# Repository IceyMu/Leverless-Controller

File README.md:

# Leverless-Controller
 A Leverless Controller for Fighting Games

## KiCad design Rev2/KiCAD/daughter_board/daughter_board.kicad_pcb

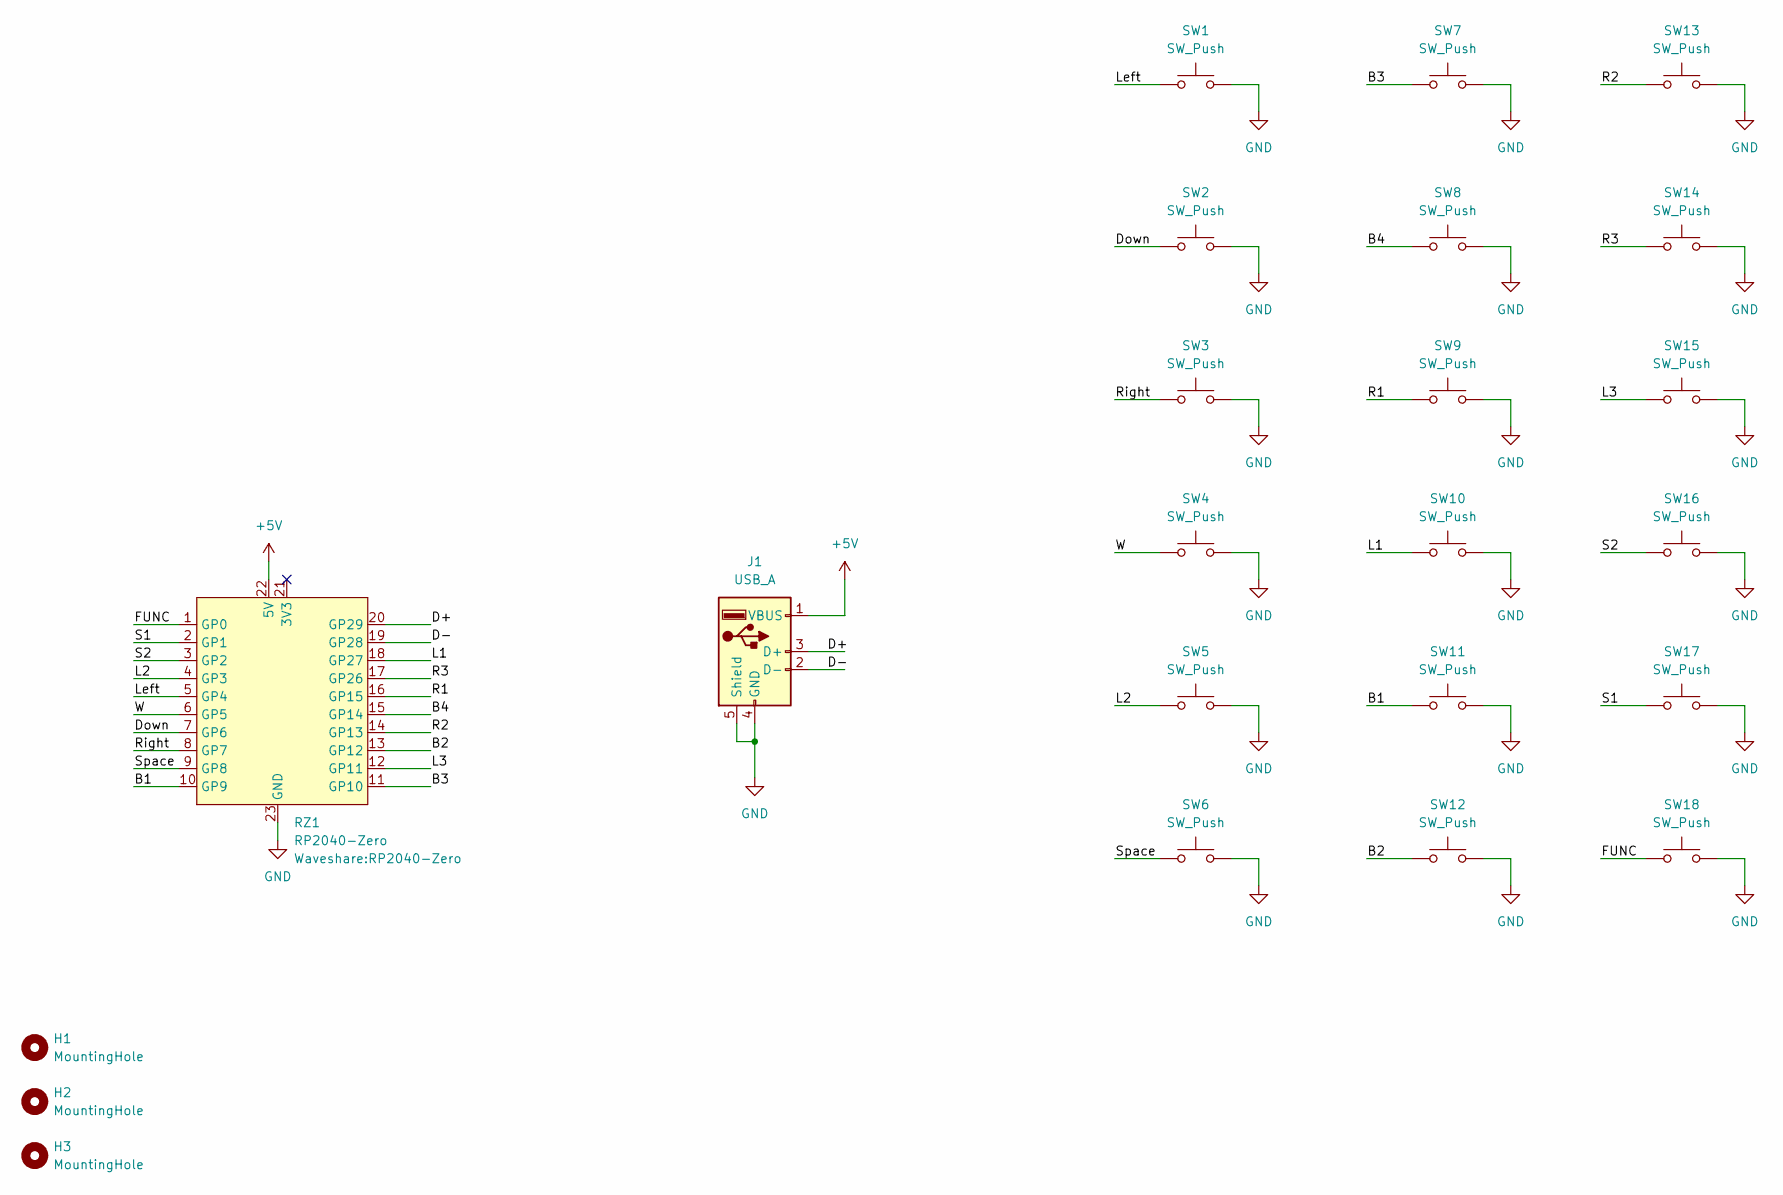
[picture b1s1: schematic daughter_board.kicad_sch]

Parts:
H1, H2, H3: MountingHole; MountingHole_3.2mm_M3
J1: USB_A; USB_A_TE_292303-7_Horizontal
RZ1: RP2040-Zero
SW1, SW2, SW3, SW4, SW5, SW6, SW7, SW8, SW9, SW10, SW11, SW12, SW13, SW14, SW15: SW_Push; SW_Gateron_LowProfile_THT
SW16, SW17, SW18: SW_Push; 6x6 vertical button

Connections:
+5V: J1.1 (VBUS), RZ1.22 (5V)
/B1: RZ1.10 (GP9), SW11.1
/B2: RZ1.13 (GP12), SW12.1
/B3: RZ1.11 (GP10), SW7.1
/B4: RZ1.15 (GP14), SW8.1
/D+: J1.3 (D+), RZ1.20 (GP29)
/D-: J1.2 (D-), RZ1.19 (GP28)
/Down: RZ1.7 (GP6), SW2.1
/FUNC: RZ1.1 (GP0), SW18.1
/L1: RZ1.18 (GP27), SW10.1
/L2: RZ1.4 (GP3), SW5.1
/L3: RZ1.12 (GP11), SW15.1
/Left: RZ1.5 (GP4), SW1.1
/R1: RZ1.16 (GP15), SW9.1
/R2: RZ1.14 (GP13), SW13.1
/R3: RZ1.17 (GP26), SW14.1
/Right: RZ1.8 (GP7), SW3.1
/S1: RZ1.2 (GP1), SW17.1
/S2: RZ1.3 (GP2), SW16.1
/Space: RZ1.9 (GP8), SW6.1
/W: RZ1.6 (GP5), SW4.1
GND: J1.4 (GND), J1.5 (Shield), RZ1.23 (GND), SW1.2, SW2.2, SW3.2, SW4.2, SW5.2, SW6.2, SW7.2, SW8.2, SW9.2, SW10.2, SW11.2, SW12.2, SW13.2, SW14.2, SW15.2, SW16.2, SW17.2, SW18.2

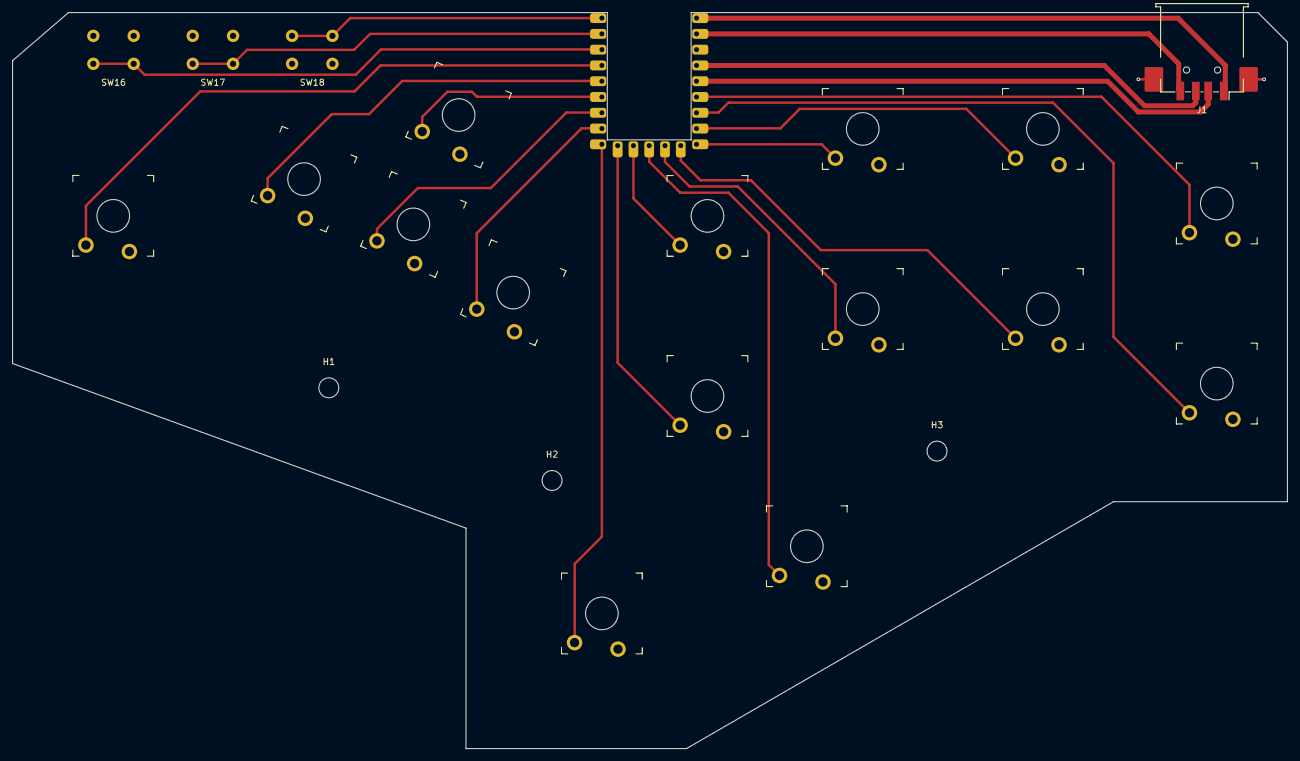
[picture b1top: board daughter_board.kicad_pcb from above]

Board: 2 copper layers, 205.2 x 118.5 mm, 23 parts (1 on the bottom side), 22 nets.

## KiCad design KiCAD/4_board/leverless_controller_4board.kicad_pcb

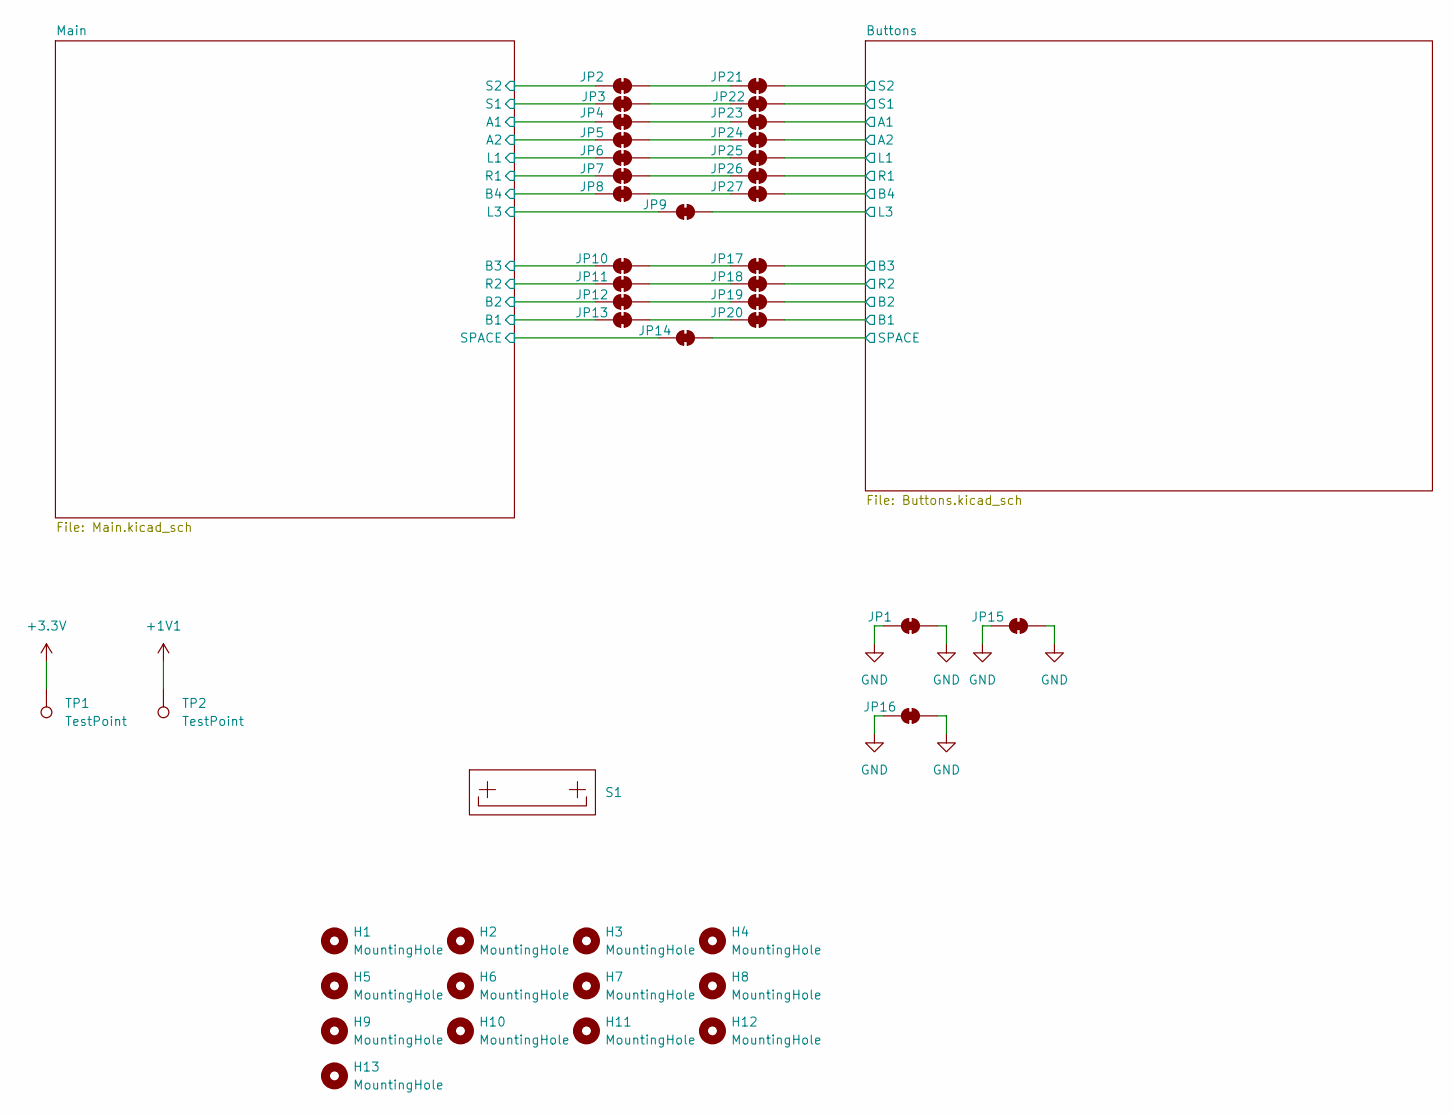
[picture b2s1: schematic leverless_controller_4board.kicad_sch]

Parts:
H1, H2, H3, H4, H5, H6, H7, H8, H9, H10, H11, H12, H13: MountingHole; MountingHole_3.2mm_M3
JP1, JP2, JP3, JP4, JP5, JP6, JP7, JP8, JP9, JP10, JP11, JP12, JP13, JP14, JP15, JP16, JP17, JP18, JP19, JP20, JP21, JP22, JP23, JP24, JP25, JP26, JP27: SolderJumper_2_Bridged; EdgeSolderJumper-2_P1.3mm_Bridged_RoundedPad1.0x1.5mm
S1: Stabilizer_Cherry_MX_2.00u
TP1, TP2: TestPoint; TestPoint_THTPad_1.0x1.0mm_Drill0.5mm

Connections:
+1V1: TP2.1; also elsewhere on the board
+3.3V: TP1.1; also elsewhere on the board
/Buttons/A1: JP23.2 (B); also elsewhere on the board
/Buttons/A2: JP24.2 (B); also elsewhere on the board
/Buttons/B1: JP20.2 (B); also elsewhere on the board
/Buttons/B2: JP19.2 (B); also elsewhere on the board
/Buttons/B3: JP17.2 (B); also elsewhere on the board
/Buttons/B4: JP27.2 (B); also elsewhere on the board
/Buttons/L1: JP25.2 (B); also elsewhere on the board
/Buttons/L3: JP9.2 (B); also elsewhere on the board
/Buttons/R1: JP26.2 (B); also elsewhere on the board
/Buttons/R2: JP18.2 (B); also elsewhere on the board
/Buttons/S1: JP22.2 (B); also elsewhere on the board
/Buttons/S2: JP21.2 (B); also elsewhere on the board
/Buttons/SPACE: JP14.2 (B); also elsewhere on the board
/Main/A1: JP4.1 (A); also elsewhere on the board
/Main/A2: JP5.1 (A); also elsewhere on the board
/Main/B1: JP13.1 (A); also elsewhere on the board
/Main/B2: JP12.1 (A); also elsewhere on the board
/Main/B3: JP10.1 (A); also elsewhere on the board
/Main/B4: JP8.1 (A); also elsewhere on the board
/Main/L1: JP6.1 (A); also elsewhere on the board
/Main/L3: JP9.1 (A); also elsewhere on the board
/Main/R1: JP7.1 (A); also elsewhere on the board
/Main/R2: JP11.1 (A); also elsewhere on the board
/Main/S1: JP3.1 (A); also elsewhere on the board
/Main/S2: JP2.1 (A); also elsewhere on the board
/Main/SPACE: JP14.1 (A); also elsewhere on the board
GND: JP1.1 (A), JP1.2 (B), JP15.1 (A), JP15.2 (B), JP16.1 (A), JP16.2 (B); also elsewhere on the board
unnamed: JP2.2 (B), JP21.1 (A)
unnamed: JP10.2 (B), JP17.1 (A)
unnamed: JP11.2 (B), JP18.1 (A)
unnamed: JP12.2 (B), JP19.1 (A)
unnamed: JP13.2 (B), JP20.1 (A)
unnamed: JP3.2 (B), JP22.1 (A)
unnamed: JP4.2 (B), JP23.1 (A)
unnamed: JP5.2 (B), JP24.1 (A)
unnamed: JP6.2 (B), JP25.1 (A)
unnamed: JP7.2 (B), JP26.1 (A)
unnamed: JP8.2 (B), JP27.1 (A)

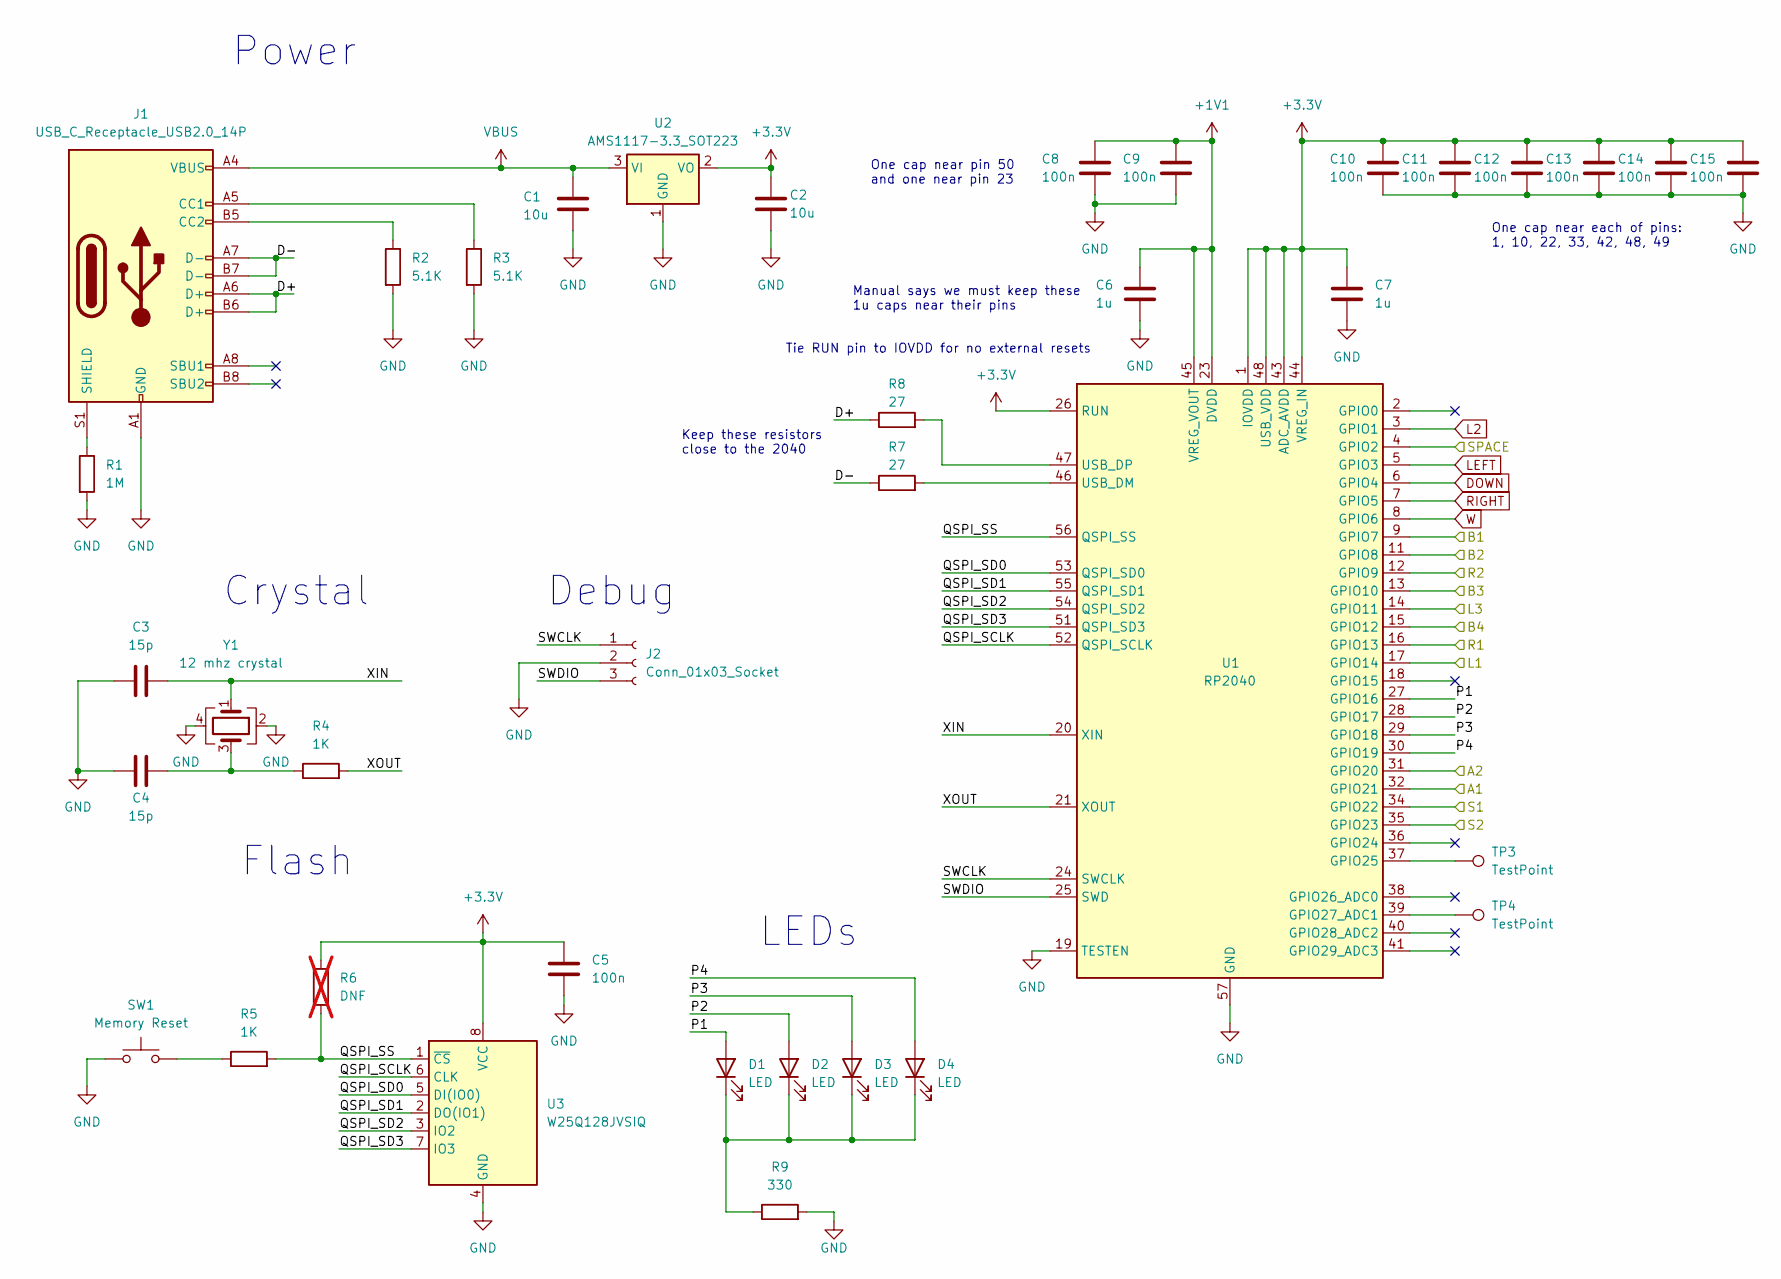
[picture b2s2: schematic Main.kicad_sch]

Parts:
C1, C2: 10u; C_0402_1005Metric; LCSC C15525
C3, C4: 15p; C_0402_1005Metric; LCSC C1548
C5, C8, C9, C10, C11, C12, C13, C14, C15: 100n; C_0402_1005Metric; LCSC C1525
C6, C7: 1u; C_0402_1005Metric; LCSC C52923
D1, D2, D3, D4: LED; LED_0805_2012Metric
J1: USB_C_Receptacle_USB2.0_14P; USB_C_Receptacle_C6332272; LCSC C6332272
J2: Conn_01x03_Socket; Debug_Points
R1: 1M; R_0402_1005Metric; LCSC C26083
R2, R3: 5.1K; R_0402_1005Metric; LCSC C25905
R4, R5: 1K; R_0402_1005Metric; LCSC C11702
R6: DNF; R_0402_1005Metric_Pad0.72x0.64mm_HandSolder; not fitted
R7, R8: 27; R_0402_1005Metric; LCSC C25190
R9: 330; R_0402_1005Metric; LCSC C25104
SW1: Memory Reset; SW_TS-1187A-C-A-B; LCSC C318884
TP3, TP4: TestPoint; TestPoint_Pad_D1.0mm
U1: RP2040; QFN-56-1EP_7x7mm_P0.4mm_EP3.2x3.2mm; LCSC C2040
U2: AMS1117-3.3_SOT223; LDO_AMS1117-3.3; LCSC C6186
U3: W25Q128JVSIQ; SOIC-8_5.23x5.23mm_P1.27mm; LCSC C97521
Y1: 12 mhz crystal; Crystal_SMD_3225-4Pin_3.2x2.5mm; LCSC C9002

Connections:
+1V1: C6.1, C8.1, C9.1, U1.23 (DVDD), U1.45 (VREG_VOUT), U1.50 (DVDD); also elsewhere on the board
+3.3V: C2.1, C5.1, C7.1, C10.1, C11.1, C12.1, C13.1, C14.1, C15.1, R6.1, U1.1 (IOVDD), U1.10 (IOVDD), U1.22 (IOVDD), U1.26 (RUN), U1.33 (IOVDD), U1.42 (IOVDD), U1.43 (ADC_AVDD), U1.44 (VREG_IN), U1.48 (USB_VDD), U1.49 (IOVDD), U2.2 (VO), U3.8 (VCC); also elsewhere on the board
/Main/A1: U1.32 (GPIO21); also elsewhere on the board
/Main/A2: U1.31 (GPIO20); also elsewhere on the board
/Main/B1: U1.9 (GPIO7); also elsewhere on the board
/Main/B2: U1.11 (GPIO8); also elsewhere on the board
/Main/B3: U1.13 (GPIO10); also elsewhere on the board
/Main/B4: U1.15 (GPIO12); also elsewhere on the board
/Main/D+: J1.A6 (D+), J1.B6 (D+), R8.1
/Main/D-: J1.A7 (D-), J1.B7 (D-), R7.1
/Main/L1: U1.17 (GPIO14); also elsewhere on the board
/Main/L3: U1.14 (GPIO11); also elsewhere on the board
/Main/P1: D1.2 (A), U1.27 (GPIO16)
/Main/P2: D2.2 (A), U1.28 (GPIO17)
/Main/P3: D3.2 (A), U1.29 (GPIO18)
/Main/P4: D4.2 (A), U1.30 (GPIO19)
/Main/QSPI_SCLK: U1.52 (QSPI_SCLK), U3.6 (CLK)
/Main/QSPI_SD0: U1.53 (QSPI_SD0), U3.5 (DI(IO0))
/Main/QSPI_SD1: U1.55 (QSPI_SD1), U3.2 (DO(IO1))
/Main/QSPI_SD2: U1.54 (QSPI_SD2), U3.3 (IO2)
/Main/QSPI_SD3: U1.51 (QSPI_SD3), U3.7 (IO3)
/Main/QSPI_SS: R5.2, R6.2, U1.56 (QSPI_SS), U3.1 (~CS)
/Main/R1: U1.16 (GPIO13); also elsewhere on the board
/Main/R2: U1.12 (GPIO9); also elsewhere on the board
/Main/S1: U1.34 (GPIO22); also elsewhere on the board
/Main/S2: U1.35 (GPIO23); also elsewhere on the board
/Main/SPACE: U1.4 (GPIO2); also elsewhere on the board
/Main/SWCLK: J2.1, U1.24 (SWCLK)
/Main/SWDIO: J2.3, U1.25 (SWD)
/Main/XIN: C3.2, U1.20 (XIN), Y1.1
/Main/XOUT: R4.2, U1.21 (XOUT)
DOWN: U1.6 (GPIO4); also elsewhere on the board
GND: C1.2, C2.2, C3.1, C4.1, C5.2, C6.2, C7.2, C8.2, C9.2, C10.2, C11.2, C12.2, C13.2, C14.2, C15.2, J1.A1 (GND), J1.A12 (GND), J1.B1 (GND), J1.B12 (GND), J2.2, R1.2, R2.2, R3.2, R9.2, SW1.1, U1.19 (TESTEN), U1.57 (GND), U2.1 (GND), U3.4 (GND), Y1.2, Y1.4; also elsewhere on the board
L2: U1.3 (GPIO1); also elsewhere on the board
LEFT: U1.5 (GPIO3); also elsewhere on the board
unnamed: C4.2, R4.1, Y1.3
unnamed: D1.1 (K), D2.1 (K), D3.1 (K), D4.1 (K), R9.1
unnamed: J1.A5 (CC1), R3.1
unnamed: J1.B5 (CC2), R2.1
unnamed: J1.S1 (SHIELD), R1.1
unnamed: R5.1, SW1.2
unnamed: TP3.1, U1.37 (GPIO25)
unnamed: TP4.1, U1.39 (GPIO27_ADC1)
unnamed: R7.2, U1.46 (USB_DM)
unnamed: R8.2, U1.47 (USB_DP)
RIGHT: U1.7 (GPIO5); also elsewhere on the board
VBUS: C1.1, J1.A4 (VBUS), J1.A9 (VBUS), J1.B4 (VBUS), J1.B9 (VBUS), U2.3 (VI)
W: U1.8 (GPIO6); also elsewhere on the board

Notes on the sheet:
Crystal
Keep these resistors close to the 2040
Flash
Tie RUN pin to IOVDD for no external resets
Debug
One cap near each of pins: 1, 10, 22, 33, 42, 48, 49
Manual says we must keep these 1u caps near their pins
One cap near pin 50 and one near pin 23
LEDs
Power

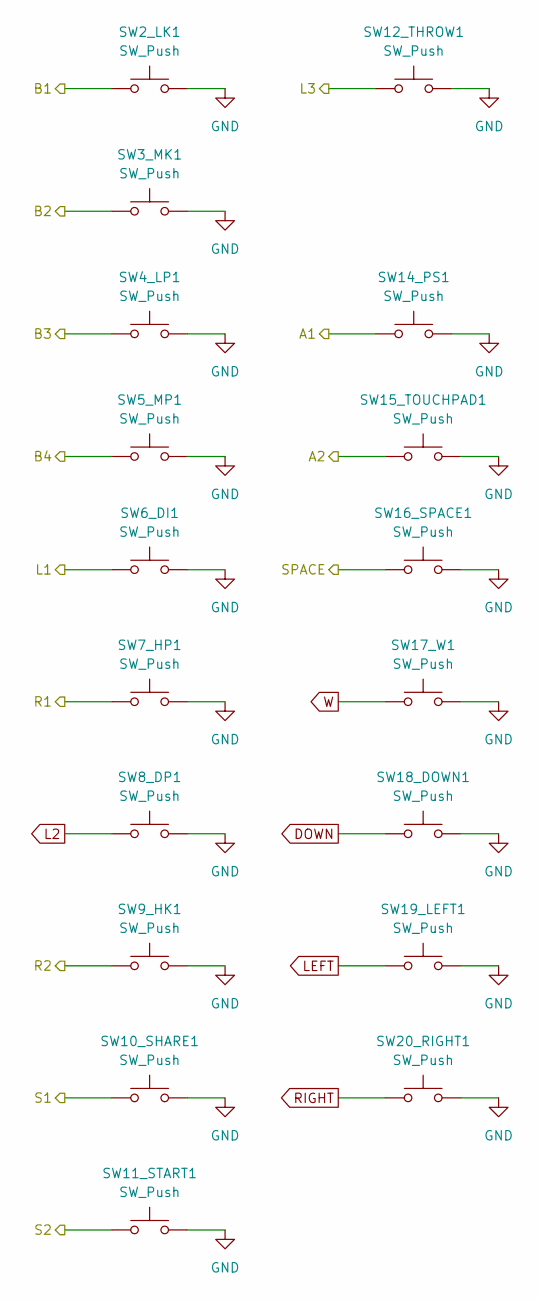
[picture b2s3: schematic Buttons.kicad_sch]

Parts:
SW2_LK1, SW3_MK1, SW4_LP1, SW5_MP1, SW6_DI1, SW7_HP1, SW8_DP1, SW9_HK1, SW12_THROW1, SW16_SPACE1: SW_Push; SW_Cherry_MX_PCB
SW10_SHARE1, SW11_START1, SW14_PS1, SW15_TOUCHPAD1: SW_Push; SW_SPST_6x12
SW17_W1, SW18_DOWN1, SW19_LEFT1, SW20_RIGHT1: SW_Push; SW_Cherry_MX_PCB_1.00u

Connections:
/Buttons/A1: SW14_PS1.1; also elsewhere on the board
/Buttons/A2: SW15_TOUCHPAD1.1; also elsewhere on the board
/Buttons/B1: SW2_LK1.1; also elsewhere on the board
/Buttons/B2: SW3_MK1.1; also elsewhere on the board
/Buttons/B3: SW4_LP1.1; also elsewhere on the board
/Buttons/B4: SW5_MP1.1; also elsewhere on the board
/Buttons/L1: SW6_DI1.1; also elsewhere on the board
/Buttons/L3: SW12_THROW1.1; also elsewhere on the board
/Buttons/R1: SW7_HP1.1; also elsewhere on the board
/Buttons/R2: SW9_HK1.1; also elsewhere on the board
/Buttons/S1: SW10_SHARE1.1; also elsewhere on the board
/Buttons/S2: SW11_START1.1; also elsewhere on the board
/Buttons/SPACE: SW16_SPACE1.1; also elsewhere on the board
DOWN: SW18_DOWN1.1; also elsewhere on the board
GND: SW2_LK1.2, SW3_MK1.2, SW4_LP1.2, SW5_MP1.2, SW6_DI1.2, SW7_HP1.2, SW8_DP1.2, SW9_HK1.2, SW10_SHARE1.2, SW11_START1.2, SW12_THROW1.2, SW14_PS1.2, SW15_TOUCHPAD1.2, SW16_SPACE1.2, SW17_W1.2, SW18_DOWN1.2, SW19_LEFT1.2, SW20_RIGHT1.2; also elsewhere on the board
L2: SW8_DP1.1; also elsewhere on the board
LEFT: SW19_LEFT1.1; also elsewhere on the board
RIGHT: SW20_RIGHT1.1; also elsewhere on the board
W: SW17_W1.1; also elsewhere on the board

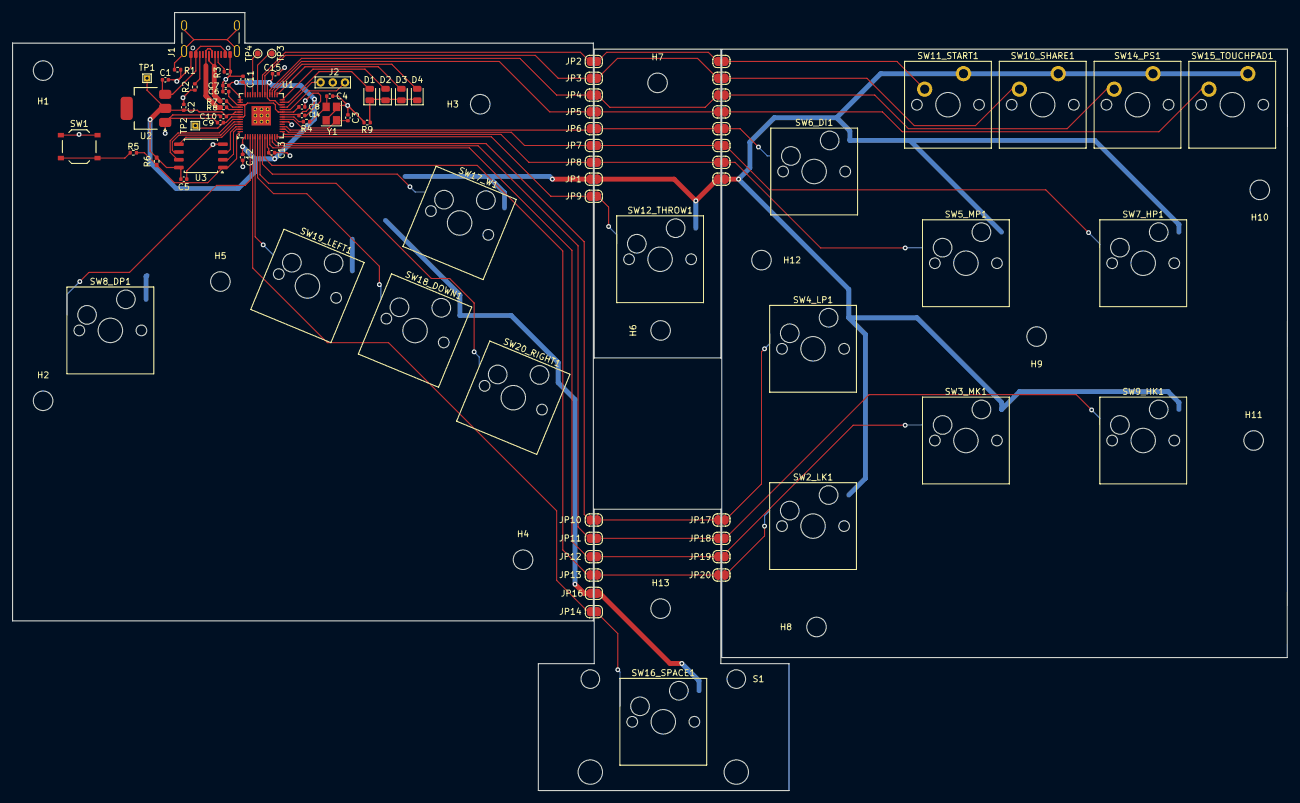
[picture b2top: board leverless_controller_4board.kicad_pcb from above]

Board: 2 copper layers, 208.5 x 127.2 mm, 102 parts (0 on the bottom side), 72 nets.

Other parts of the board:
B1, B2, B3, B4: Board

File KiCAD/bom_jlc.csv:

"Id";"Designator";"Footprint";"Quantity";"Designation";"Supplier and ref";
1;"R9";"R_0402_1005Metric";1;"330";;;
2;"D4,D3,D2,D1";"LED_0603_1608Metric";4;"LED";;;
3;"TP4,TP3";"TestPoint_Pad_D1.0mm";2;"TestPoint";;;
4;"TP2,TP1";"TestPoint_THTPad_1.0x1.0mm_Drill0.5mm";2;"TestPoint";;;
5;"C2,C18,C17,C1";"C_0402_1005Metric";4;"4.7u";;;
6;",,,,,,,,";"";9;"";;;
7;"Y1";"Crystal_SMD_3225-4Pin_3.2x2.5mm";1;"12 mhz crystal";;;
8;"C9,C8,C15,C16,C10,C12,C5,C13,C14,C11";"C_0402_1005Metric";10;"100n";;;
9;"C7,C6";"C_0402_1005Metric";2;"1u";;;
10;"SW1";"SW_TS-1187A-C-A-B";1;"Memory Reset";;;
11;"R4,R5";"R_0402_1005Metric";2;"1K";;;
12;"R2,R3";"R_0402_1005Metric";2;"5.1K";;;
13;"U2";"SOT-223-3_TabPin2";1;"AMS1117-3.3_SOT223";;;
14;"C3,C4";"C_0402_1005Metric";2;"15p";;;
15;"R7,R8";"R_0402_1005Metric";2;"27";;;
16;"U1";"QFN-56-1EP_7x7mm_P0.4mm_EP3.2x3.2mm";1;"RP2040";;;
17;"J1";"USB_C_Receptacle_U262-161N-4BVC11";1;"USB_C_Receptacle_USB2.0_14P";;;
18;"U3";"SOIC-8_5.23x5.23mm_P1.27mm";1;"W25Q128JVSIQ";;;
19;"R1";"R_0402_1005Metric";1;"1M";;;

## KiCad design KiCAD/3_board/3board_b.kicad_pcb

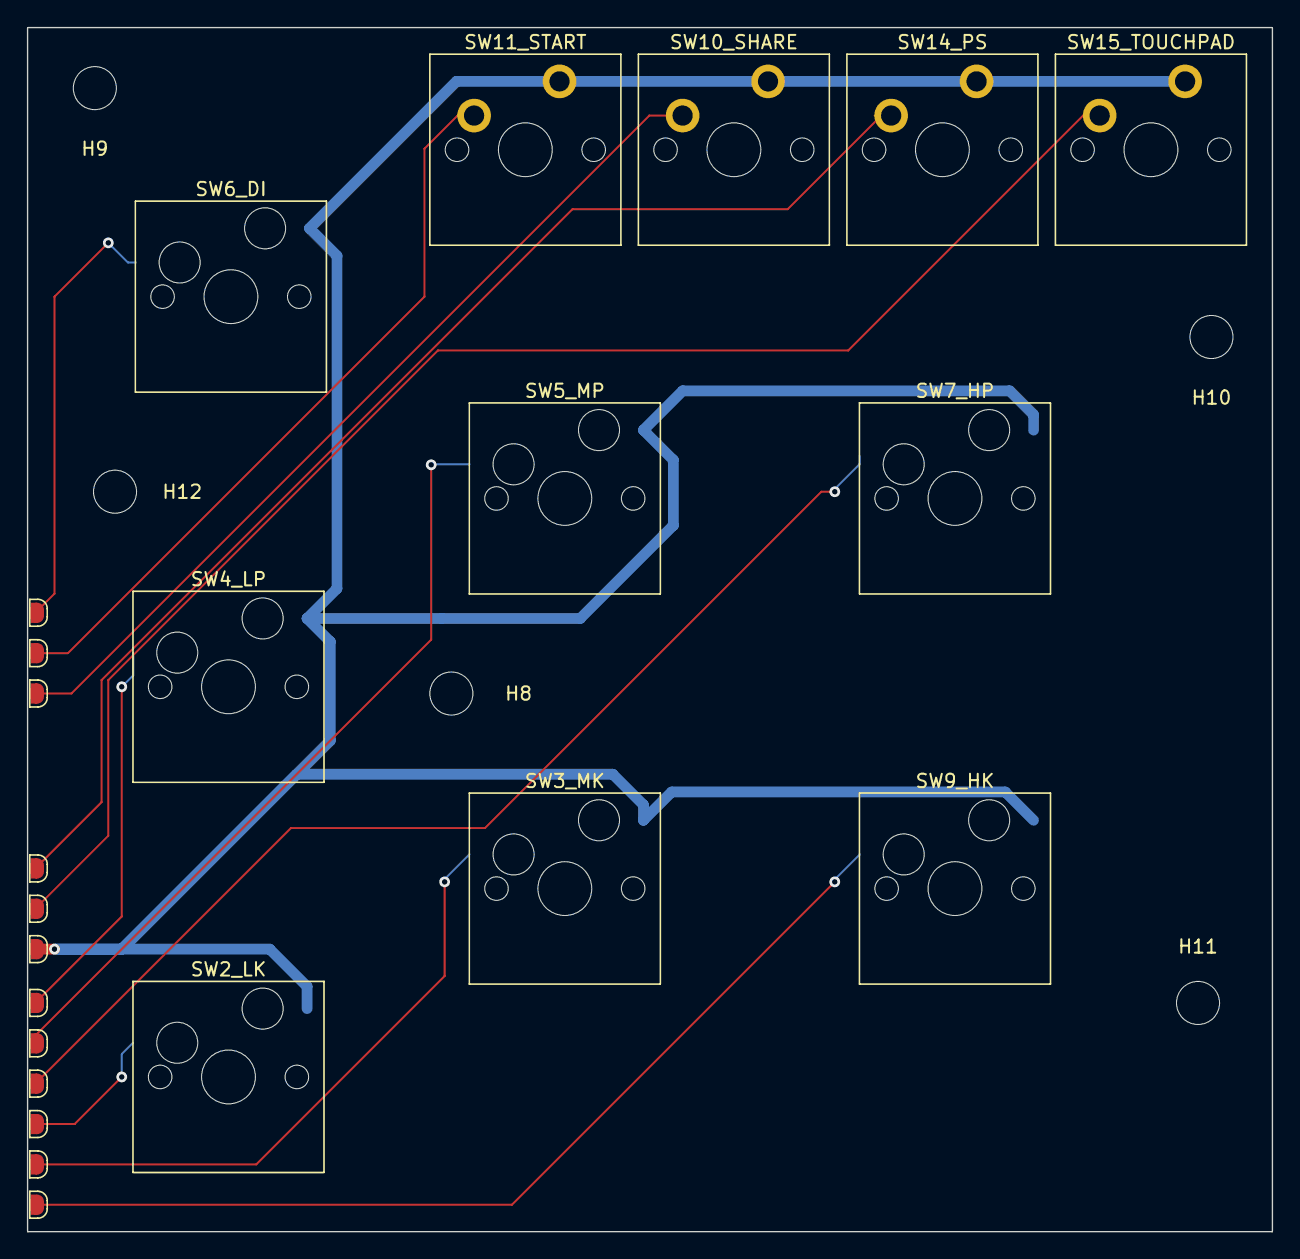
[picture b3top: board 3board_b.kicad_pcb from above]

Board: 2 copper layers, 92.5 x 89.5 mm, 29 parts (0 on the bottom side), 12 nets.

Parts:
B2: Board
H8, H9, H10, H11, H12: MountingHole; MountingHole_3.2mm_M3
JP15, JP17, JP18, JP19, JP20, JP21, JP22, JP23, JP24, JP25, JP26, JP27: SolderJumper_2_Bridged; EdgeSolderJumper-2_Right_Half
SW2_LK, SW3_MK, SW4_LP, SW5_MP, SW6_DI, SW7_HP, SW9_HK: SW_Push; SW_Hotswap_Kailh_MX
SW10_SHARE, SW11_START, SW14_PS, SW15_TOUCHPAD: SW_Push; SW_Cherry_MX_PCB

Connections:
/Buttons/A1: JP23.2 (B), SW14_PS.1
/Buttons/A2: JP24.2 (B), SW15_TOUCHPAD.1
/Buttons/B1: JP20.2 (B), SW2_LK.1
/Buttons/B2: JP19.2 (B), SW3_MK.1
/Buttons/B3: JP17.2 (B), SW4_LP.1
/Buttons/B4: JP27.2 (B), SW5_MP.1
/Buttons/L1: JP25.2 (B), SW6_DI.1
/Buttons/R1: JP26.2 (B), SW7_HP.1
/Buttons/R2: JP18.2 (B), SW9_HK.1
/Buttons/S1: JP22.2 (B), SW10_SHARE.1
/Buttons/S2: JP21.2 (B), SW11_START.1
GND: JP15.2 (B), SW2_LK.2, SW3_MK.2, SW4_LP.2, SW5_MP.2, SW6_DI.2, SW7_HP.2, SW9_HK.2, SW10_SHARE.2, SW11_START.2, SW14_PS.2, SW15_TOUCHPAD.2

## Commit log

2024-07-18 Start PCB Layout
2024-07-18 PCB First Draft
2024-07-19 Make PCB and case fit together
2024-07-19 First DFM pass
2024-07-21 Second DFM pass
2024-07-22 Add foot prints
2024-07-23 Add multiboard configurations
2024-07-24 Panelize 4 board design
2024-07-25 4 board DFM pass
2024-07-25 Update Case for 4 board
2024-07-26 Add silkscreen images
2024-07-29 PCB Order Version
2024-07-29 Add 3 Board (New Order Version)
2024-07-29 Fix missing connection to HP
2024-07-30 Update CAD model based on PCB order
2024-07-30 Remove Outdated PCB Configurations
2024-07-31 Correct 27ohm resistor footprint to 0603 and add 10mm button
2024-08-16 Add Keyswitch Plate and Light Guide
2024-08-16 Update STLs
2024-08-21 Add revision marker to PCB
2024-08-26 Correct Board 3 Revision Marker
2024-09-16 Redo solidworks files, make rev a files match order version, make rev b
2024-09-28 Assembled Version
2024-11-24 Improve Key Stab Connection
2025-10-01 Add second revision
